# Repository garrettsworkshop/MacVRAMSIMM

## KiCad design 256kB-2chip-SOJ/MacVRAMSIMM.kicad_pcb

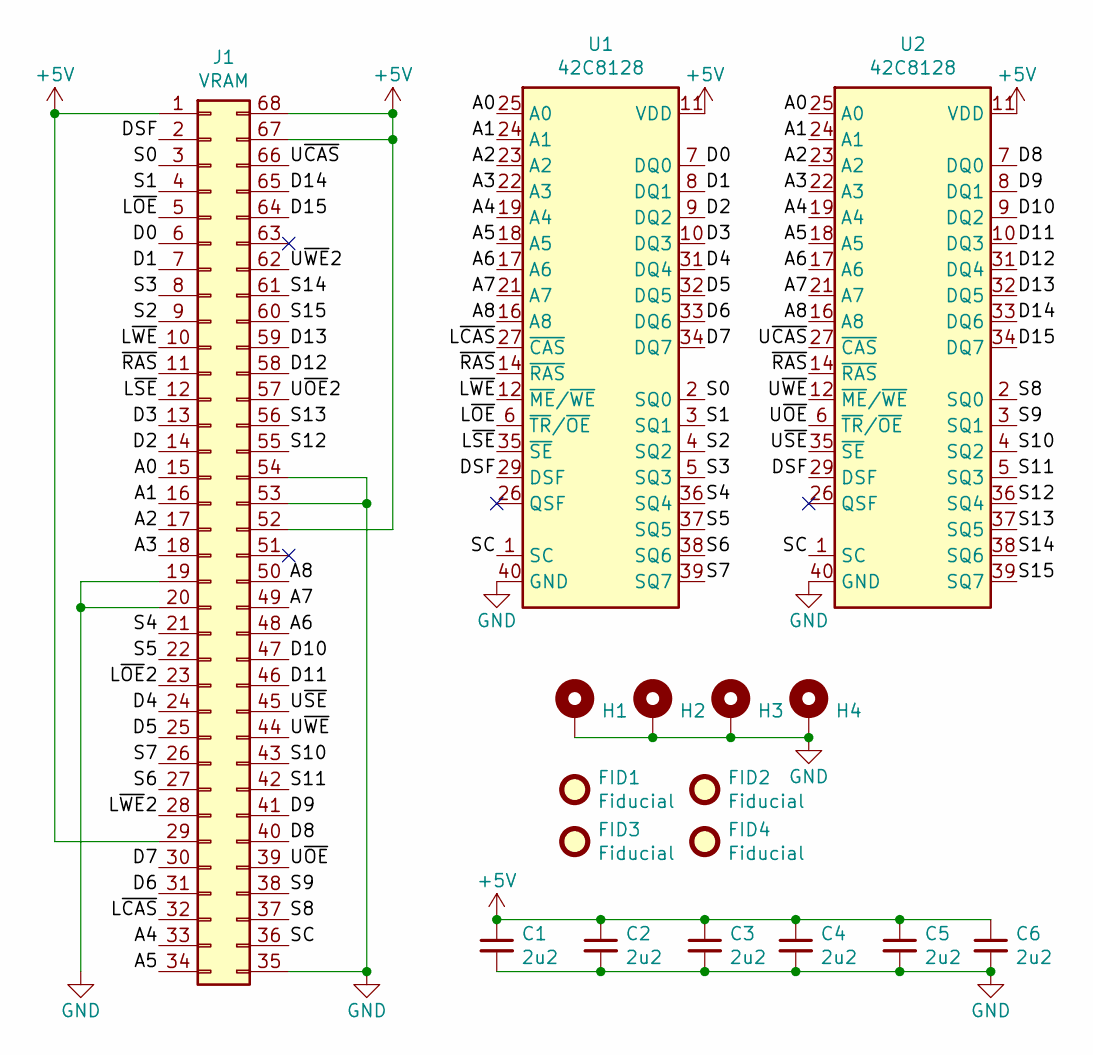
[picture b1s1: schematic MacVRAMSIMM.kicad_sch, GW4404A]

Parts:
C1, C2, C3, C4, C5, C6: 2u2; C_0805
FID1, FID2, FID3, FID4: Fiducial
H1, H2, H3, H4: PasteHole_1.1mm_PTH
J1: VRAM; MacVRAMSIMM_Edge
U1, U2: 42C8128; SOJ-40_400mil

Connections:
+5V: C1.1, C2.1, C3.1, C4.1, C5.1, C6.1, J1.1, J1.29, J1.52, J1.67, J1.68, U1.11 (VDD), U1.20 (VDD), U2.11 (VDD), U2.20 (VDD)
/A0: J1.15, U1.25 (A0), U2.25 (A0)
/A1: J1.16, U1.24 (A1), U2.24 (A1)
/A2: J1.17, U1.23 (A2), U2.23 (A2)
/A3: J1.18, U1.22 (A3), U2.22 (A3)
/A4: J1.33, U1.19 (A4), U2.19 (A4)
/A5: J1.34, U1.18 (A5), U2.18 (A5)
/A6: J1.48, U1.17 (A6), U2.17 (A6)
/A7: J1.49, U1.21 (A7), U2.21 (A7)
/A8: J1.50, U1.16 (A8), U2.16 (A8)
/D0: J1.6, U1.7 (DQ0)
/D1: J1.7, U1.8 (DQ1)
/D2: J1.14, U1.9 (DQ2)
/D3: J1.13, U1.10 (DQ3)
/D4: J1.24, U1.31 (DQ4)
/D5: J1.25, U1.32 (DQ5)
/D6: J1.31, U1.33 (DQ6)
/D7: J1.30, U1.34 (DQ7)
/D8: J1.40, U2.7 (DQ0)
/D9: J1.41, U2.8 (DQ1)
/D10: J1.47, U2.9 (DQ2)
/D11: J1.46, U2.10 (DQ3)
/D12: J1.58, U2.31 (DQ4)
/D13: J1.59, U2.32 (DQ5)
/D14: J1.65, U2.33 (DQ6)
/D15: J1.64, U2.34 (DQ7)
/DSF: J1.2, U1.29 (DSF), U2.29 (DSF)
/L~CAS: J1.32, U1.27 (~CAS)
/L~OE: J1.5, U1.6 (~TR/~OE)
/L~OE2: J1.23
/L~SE: J1.12, U1.35 (~SE)
/L~WE: J1.10, U1.12 (~ME/~WE)
/L~WE2: J1.28
/S0: J1.3, U1.2 (SQ0)
/S1: J1.4, U1.3 (SQ1)
/S2: J1.9, U1.4 (SQ2)
/S3: J1.8, U1.5 (SQ3)
/S4: J1.21, U1.36 (SQ4)
/S5: J1.22, U1.37 (SQ5)
/S6: J1.27, U1.38 (SQ6)
/S7: J1.26, U1.39 (SQ7)
/S8: J1.37, U2.2 (SQ0)
/S9: J1.38, U2.3 (SQ1)
/S10: J1.43, U2.4 (SQ2)
/S11: J1.42, U2.5 (SQ3)
/S12: J1.55, U2.36 (SQ4)
/S13: J1.56, U2.37 (SQ5)
/S14: J1.61, U2.38 (SQ6)
/S15: J1.60, U2.39 (SQ7)
/SC: J1.36, U1.1 (SC), U2.1 (SC)
/U~CAS: J1.66, U2.27 (~CAS)
/U~OE: J1.39, U2.6 (~TR/~OE)
/U~OE2: J1.57
/U~SE: J1.45, U2.35 (~SE)
/U~WE: J1.44, U2.12 (~ME/~WE)
/U~WE2: J1.62
/~RAS: J1.11, U1.14 (~RAS), U2.14 (~RAS)
GND: C1.2, C2.2, C3.2, C4.2, C5.2, C6.2, H1.1, H2.1, H3.1, H4.1, J1.19, J1.20, J1.35, J1.53, J1.54, U1.30 (GND), U1.40 (GND), U2.30 (GND), U2.40 (GND)

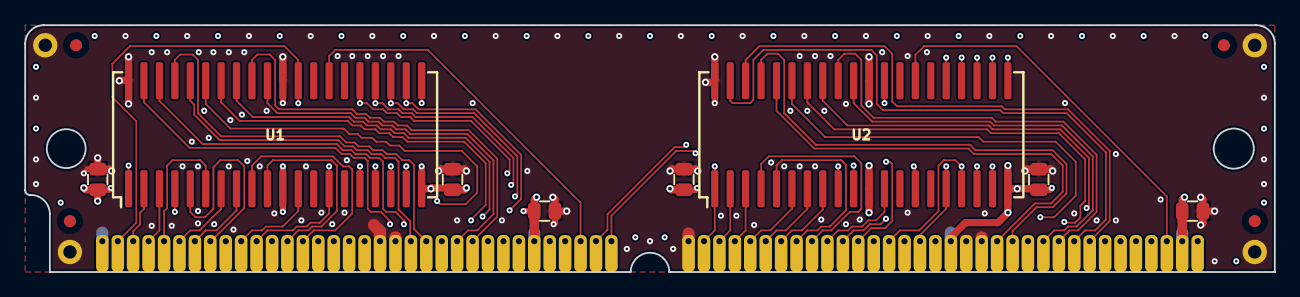
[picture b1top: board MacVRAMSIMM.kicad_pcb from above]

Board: 4 copper layers, 102.9 x 20.3 mm, 17 parts (0 on the bottom side), 54 nets.

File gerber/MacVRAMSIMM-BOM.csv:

Reference, Quantity, Value, Footprint, Datasheet
C1 C2 C3 C4 C5 C6 ,6,"2u2","stdpads:C_0805",""
FID1 FID2 FID3 FID4 ,4,"Fiducial","stdpads:Fiducial",""
H1 H2 H3 H4 ,4," ","stdpads:PasteHole_1.1mm_PTH",""
J1 ,1,"VRAM","stdpads:MacVRAMSIMM_Edge",""
U1 U2 ,2,"42C8255","stdpads:SOJ-40-400mil-Skinny",""

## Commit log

2021-05-29 Done?
2021-05-31 Fabbed
2021-05-31 Documentation update
2021-08-06 Manual done?
2022-02-06 Migrate to KiCAD 6
2022-02-06 Switch to KiCAD 6 3dmodels
2023-02-28 Remove pictures? And add somem ore
